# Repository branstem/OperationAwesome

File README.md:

OperationAwesome
================

ECE411 Project

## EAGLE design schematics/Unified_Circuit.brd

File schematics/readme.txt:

This folder was made for circuits.

All unique symbols not shipped with eaglecad should be added to symbols.lbr. 

This library file should also be added to eagles library path to load and 
edit the file.

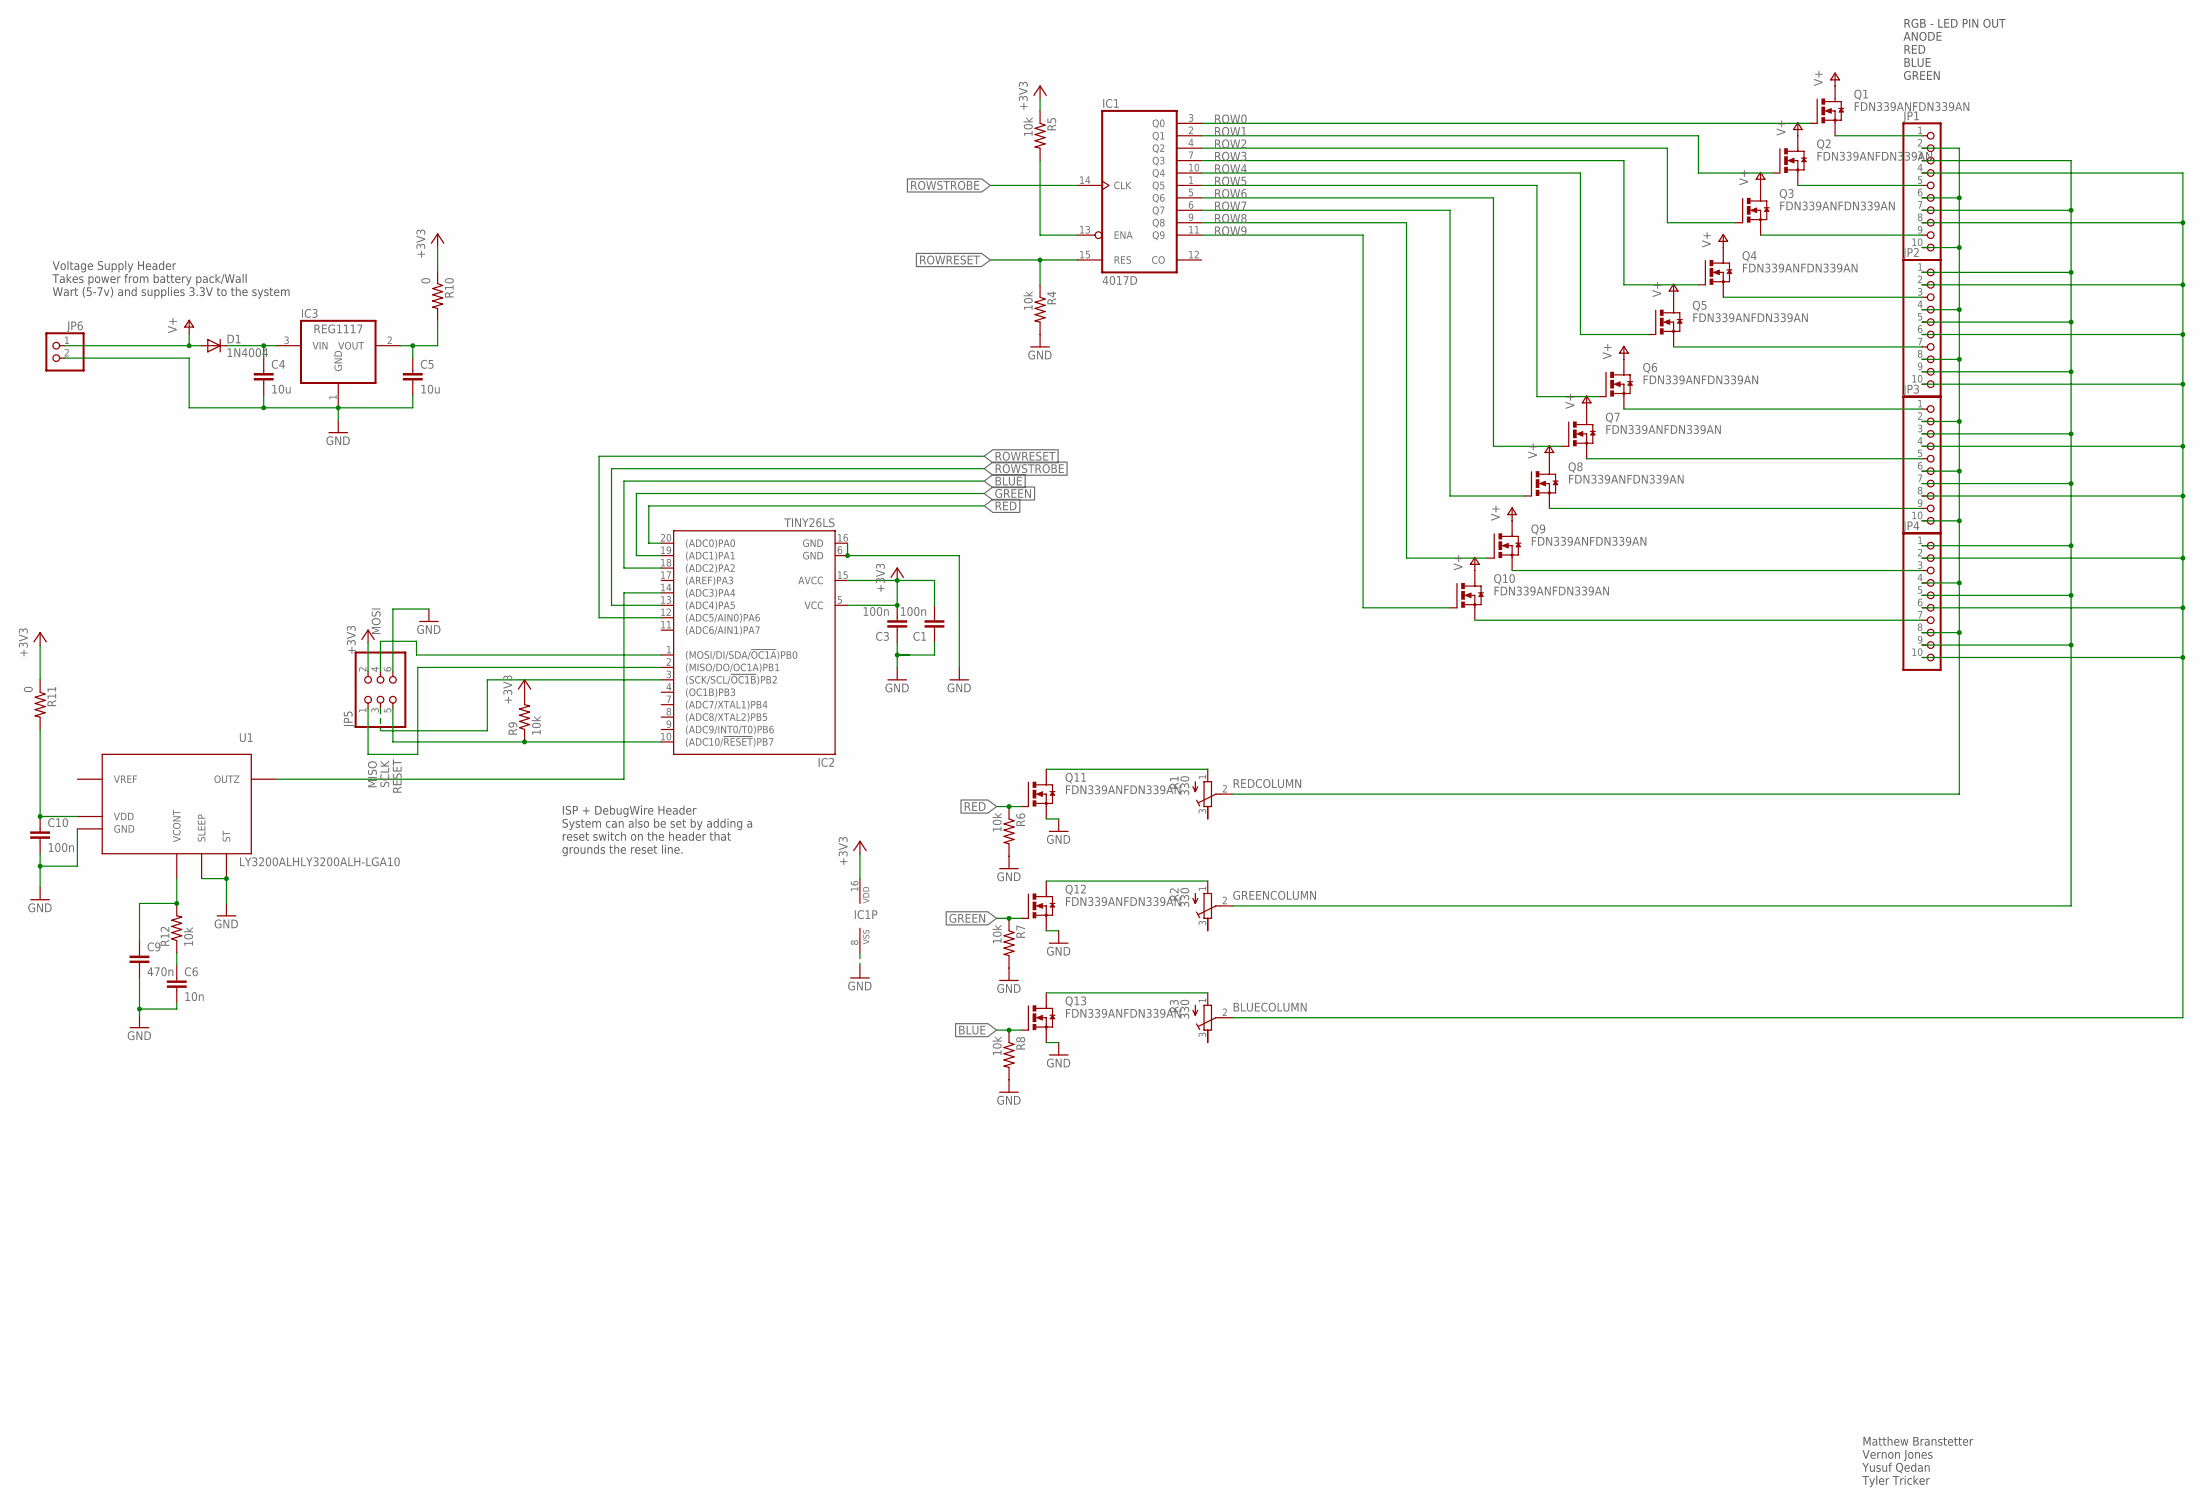
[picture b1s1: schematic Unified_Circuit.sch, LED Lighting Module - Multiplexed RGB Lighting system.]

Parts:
C1, C3, C10: 100n; C0805
C4, C5: 10u; C0805
C6: 10n; C0805
C9: 470n; C0805
D1: 1N4004; DO41-10
IC1: 4017D; SO16
IC2: TINY26LS; SO20L
IC3: REG1117; SOT223
JP1, JP2, JP3, JP4: PINHD-1X10/90; 1X10/90
JP5: PINHD-2X3; 2X03
JP6: PINHD-1X2; 1X02
Q1, Q2, Q3, Q4, Q5, Q6, Q7, Q8, Q9, Q10, Q11, Q12, Q13: FDN339ANFDN339AN; SSOT-3
R1, R2, R3: 330; RTRIM3224W
R4, R5, R6, R7, R8, R9, R12: 10k; R0805
R10, R11: 0; R0805
U1: LY3200ALHLY3200ALH-LGA10; LGA10

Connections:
+3V3: C1.2, C3.2, IC1.16 (VDD), IC2.5 (VCC), IC2.15 (AVCC), JP5.2, R5.1, R9.2, R10.1, R11.1
BLUE: IC2.18 ((ADC2)PA2), Q13.P$2 (G), R8.1
BLUECOLUMN: JP1.4, JP1.8, JP2.2, JP2.6, JP2.10, JP3.4, JP3.8, JP4.2, JP4.6, JP4.10, R3.2 (S)
GND: C1.1, C3.1, C4.2, C5.2, C6.2, C9.2, C10.2, IC1.8 (VSS), IC2.6 (GND), IC2.16 (GND), IC3.1 (GND), JP5.6, JP6.2, Q11.P$3 (S), Q12.P$3 (S), Q13.P$3 (S), R4.2, R6.2, R7.2, R8.2, U1.P$2 (ST), U1.P$4 (GND), U1.P$8 (SLEEP)
GREEN: IC2.19 ((ADC1)PA1), Q12.P$2 (G), R7.1
GREENCOLUMN: JP1.3, JP1.7, JP2.1, JP2.5, JP2.9, JP3.3, JP3.7, JP4.1, JP4.5, JP4.9, R2.2 (S)
MISO: IC2.2 ((MISO/DO/OC1A)PB1), JP5.1
MOSI: IC2.1 ((MOSI/DI/SDA/!OC1A!)PB0), JP5.4
unnamed: Q11.P$1 (D), R1.1 (A)
unnamed: Q12.P$1 (D), R2.1 (A)
unnamed: Q13.P$1 (D), R3.1 (A)
unnamed: C4.1, D1.C, IC3.3 (VIN)
unnamed: C5.1, IC3.2 (VOUT), R10.2
unnamed: IC2.14 ((ADC3)PA4), U1.P$6 (OUTZ)
unnamed: C6.1, R12.1
unnamed: JP2.3, Q4.P$3 (S)
unnamed: JP2.7, Q5.P$3 (S)
unnamed: JP1.1, Q1.P$3 (S)
unnamed: JP1.5, Q2.P$3 (S)
unnamed: JP1.9, Q3.P$3 (S)
unnamed: JP3.1, Q6.P$3 (S)
unnamed: JP3.5, Q7.P$3 (S)
unnamed: JP3.9, Q8.P$3 (S)
unnamed: JP4.3, Q9.P$3 (S)
unnamed: JP4.7, Q10.P$3 (S)
unnamed: C9.1, R12.2, U1.P$3 (VCONT)
unnamed: C10.1, R11.2, U1.P$1 (VDD), U1.P$9 (VDD)
PA1: IC1.13 (ENA), R5.2
RED: IC2.20 ((ADC0)PA0), Q11.P$2 (G), R6.1
REDCOLUMN: JP1.2, JP1.6, JP1.10, JP2.4, JP2.8, JP3.2, JP3.6, JP3.10, JP4.4, JP4.8, R1.2 (S)
RESET: IC2.10 ((ADC10/!RESET!)PB7), JP5.5, R9.1
ROW0: IC1.3 (Q0), Q1.P$2 (G)
ROW1: IC1.2 (Q1), Q2.P$2 (G)
ROW2: IC1.4 (Q2), Q3.P$2 (G)
ROW3: IC1.7 (Q3), Q4.P$2 (G)
ROW4: IC1.10 (Q4), Q5.P$2 (G)
ROW5: IC1.1 (Q5), Q6.P$2 (G)
ROW6: IC1.5 (Q6), Q7.P$2 (G)
ROW7: IC1.6 (Q7), Q8.P$2 (G)
ROW8: IC1.9 (Q8), Q9.P$2 (G)
ROW9: IC1.11 (Q9), Q10.P$2 (G)
ROWRESET: IC1.15 (RES), IC2.12 ((ADC5/AIN0)PA6), R4.1
ROWSTROBE: IC1.14 (CLK), IC2.13 ((ADC4)PA5)
SCLK: IC2.3 ((SCK/SCL/!OC1B!)PB2), JP5.3
V+: D1.A, JP6.1, Q1.P$1 (D), Q2.P$1 (D), Q3.P$1 (D), Q4.P$1 (D), Q5.P$1 (D), Q6.P$1 (D), Q7.P$1 (D), Q8.P$1 (D), Q9.P$1 (D), Q10.P$1 (D)

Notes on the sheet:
RGB - LED PIN OUT ANODE RED BLUE GREEN
ISP + DebugWire Header System can also be set by adding a reset switch on the header that grounds the reset line.
Voltage Supply Header Takes power from battery pack/Wall Wart (5-7v) and supplies 3.3V to the system
Matthew Branstetter Vernon Jones Yusuf Qedan Tyler Tricker

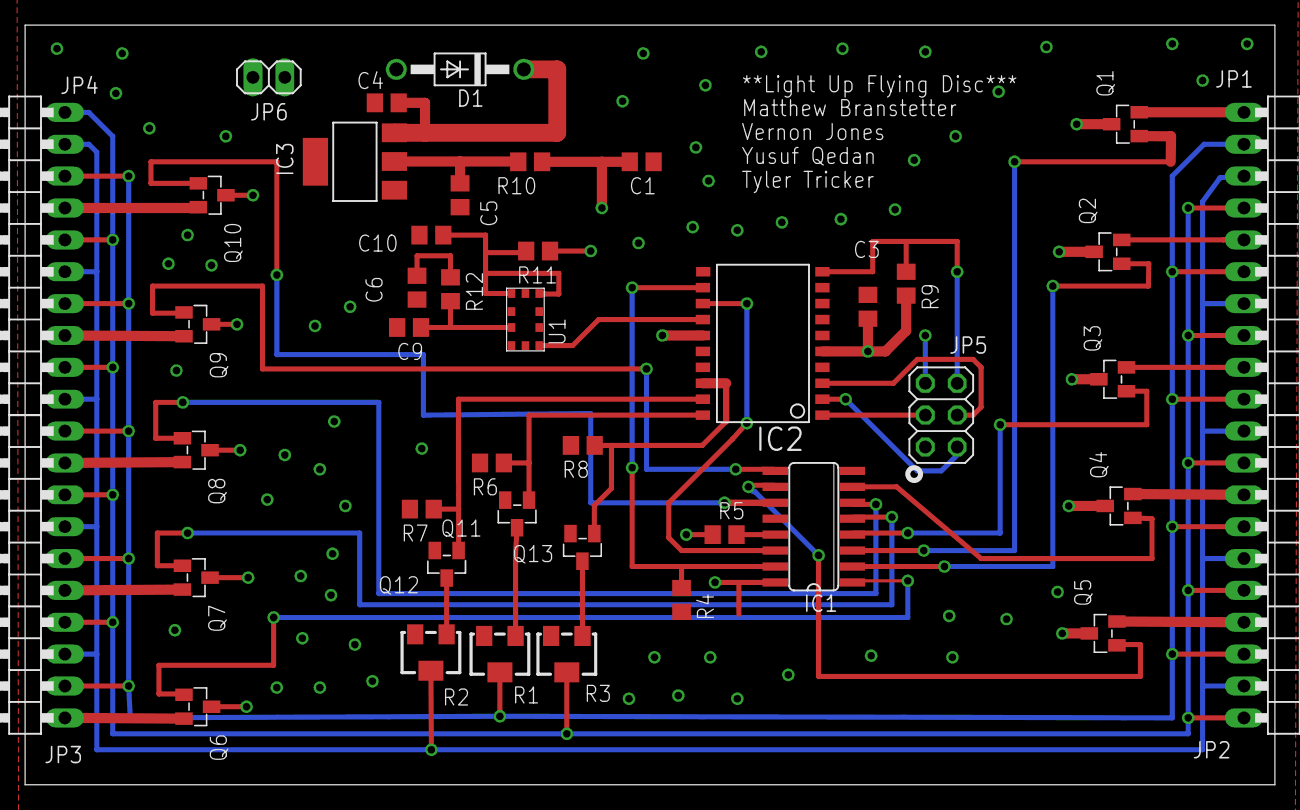
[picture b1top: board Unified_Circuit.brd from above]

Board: 2 copper layers, 99.6 x 60.6 mm, 43 parts (0 on the bottom side), 45 nets.

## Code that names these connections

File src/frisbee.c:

/*
 * frisbee.c
 *
 * Created: 10/12/2012 5:40:17 PM
 *  Author: Matthew, Vernon
 *
 * This program is free software; you can redistribute it and/or modify it
 * under the terms of the GNU Lesser General Public License as published by the
 * Free Software Foundation; either version 2.1 of the License, or (at your
 * option) any later version.
 *
 * This program is distributed in the hope that it will be useful, but
 * WITHOUT ANY WARRANTY; without even the implied warranty of
 * MERCHANTABILITY or FITNESS FOR A PARTICULAR PURPOSE.  See the GNU Lesser
 * General Public License for more details.
 *
 * You should have received a copy of the GNU Lesser General Public License along
 * with this program; if not, write to the Free Software Foundation, Inc.,
 * 51 Franklin Street, Fifth Floor, Boston, MA 02110-1301, USA.
 */


#include "frisbee.h"


void row_advance(void)
{
	// Advance to the next row
	setbit(PORTA, ROWSTROBE);
	_delay_us(10);
	//for (i=0; i<10; i++);
	clearbit(PORTA, ROWSTROBE);
}

void row_reset(void)
{
	// Reset to the first row
	setbit(PORTA, ROWRESET);
	//for (i=0; i<10; i++);
	_delay_us(10);
	clearbit(PORTA, ROWRESET);
}

void row_set_color (int red, int green, int blue)
{
	// Set the row color
	if (!PROTOTYPE)
	{
		red = !red;
		green = !green;
		blue = !blue;
	}
	if (red)
		clearbit(PORTA, LED_RED);
	else
		setbit(PORTA, LED_RED);

	// GREEN
	if (green)
		clearbit(PORTA, LED_GREEN);
	else
		setbit(PORTA, LED_GREEN);

	// BLUE
	if (blue)
		clearbit(PORTA, LED_BLUE);
	else
		setbit(PORTA, LED_BLUE);
	return;
}


void scheduler_run(struct sched_t sched[NUM_LEDS])
{
	int i;
	row_reset();
	for (i=0; i<NUM_LEDS; i++)
	{
		row_set_color(sched[i].red, sched[i].green, sched[i].blue);
		//row_set_color(1, 0, 0);
		_delay_us(200);
		//_delay_ms(1);
		//_delay_ms(1000);
		row_set_color(0, 0, 0);
		row_advance();
	}
	row_reset();
	
	return;
}

void scheduler_schedule_color(struct sched_t *sched, int red, int green, int blue)
{
	sched->red = red;
	sched->green = green;
	sched->blue = blue;
	
	return;
}

void scheduler_fill(struct sched_t sched[NUM_LEDS], int red, int green, int blue)
{
	int i;
	for (i=0; i<NUM_LEDS; i++)
		scheduler_schedule_color(&sched[i], red, green, blue);
		
	return;
}

void scheduler_rotate_left(struct sched_t sched[NUM_LEDS])
{
	int i, nexti;
	struct sched_t held_sched;
	scheduler_schedule_color(&held_sched, sched[NUM_LEDS-1].red, sched[NUM_LEDS-1].green, sched[NUM_LEDS-1].blue);
	for (i=NUM_LEDS-1; i>=0; i--)
	{
		nexti = (i-1) % NUM_LEDS;
		scheduler_schedule_color(&sched[i], sched[nexti].red, sched[nexti].green, sched[nexti].blue);
	}
	scheduler_schedule_color(&sched[0], held_sched.red, held_sched.green, held_sched.blue);
	return;
}

void scheduler_rotate_right(struct sched_t sched[NUM_LEDS])
{
	int i, nexti;
	struct sched_t held_sched;
	scheduler_schedule_color(&held_sched, sched[0].red, sched[0].green, sched[0].blue);
	for (i=0; i<NUM_LEDS; i++)
	{
		nexti = (i+1) % NUM_LEDS;
		scheduler_schedule_color(&sched[i], sched[nexti].red, sched[nexti].green, sched[nexti].blue);
	}
	scheduler_schedule_color(&sched[NUM_LEDS-1], held_sched.red, held_sched.green, held_sched.blue);
	return;
}

void scheduler_do_startup(struct sched_t sched[NUM_LEDS])
{
	int i, j;
	scheduler_fill(sched, 0, 0, 0);
	scheduler_schedule_color(&sched[0], 0, 1, 0);
	for (i=0; i<NUM_LEDS-1; i++)
	{
		for (j=0; j<60; j++)
			scheduler_run(sched);
		scheduler_rotate_left(sched);
	}
	for (i=0; i<NUM_LEDS; i++)
	{
		for (j=0; j<60; j++)
			scheduler_run(sched);
			
		scheduler_rotate_right(sched);
	}
	return;
}


void schedule_party_mode(struct sched_t sched[NUM_LEDS])
{
	int color = 0;
	int i;
	for (i=0; i<NUM_LEDS; i++)
	{
		switch (color)
		{
			case 0:
				scheduler_schedule_color(&sched[i], 1, 0, 0);
				break;
			case 1:
				scheduler_schedule_color(&sched[i], 0, 1, 0);
				break;
			case 2:
				scheduler_schedule_color(&sched[i], 0, 0, 1);
				break;
			default:
				scheduler_schedule_color(&sched[i], 1, 1, 1);
		}
		color = (color + 1) % 3;
	}
	return;
}
int init_microcontroller(void)
{
	init_ports();				// setup the ports
	init_ADC();					// setup the Analog Converter
	
	return 0;
}

void init_ports(void)
{
   setbit(DDRA, PA0);	// Set as output (LED_RED)
   setbit(DDRA, PA1);	// Set as output (LED_GREEN)
   setbit(DDRA, PA2);	// Set as output (LED_BLUE)
   clearbit(DDRA, PA3);	// Set as input AREF
   clearbit(DDRA, PA4);	// Set as input (ADC3)
   setbit(DDRA, PA5);	// Set as output (ROWSTROBE)
   setbit(DDRA, PA6);	// Set as output (ROWRESET)
   setbit(DDRA, PA7);	// Set as output 
   setbit(PORTA, PA7);
}

void init_ADC(void)
{
   setbit(ADCSRB, REFS2);	// Set voltage reference to internal 2.56V
   setbit(ADMUX, REFS1);	// Set voltage reference to internal 2.56V
   //clearbit(ADMUX, REFS1);	// Set voltage reference to internal 3.3V
   clearbit(ADMUX, REFS0);	// Set voltage reference to internal 2.56V 
   
   setbit(ADMUX, ADLAR);	// Left adjust ADC result to allow easy 8 bit reading
   
   //Using Single Conversion this code not needed
   //setbit(ADCSRA, ADATE);	// Set ADD to Auto Trigger enabled for free running
   
   setbit(ADCSRA, ADPS2);	// Set ADC pre-scalar to 64 (8 MHZ / 64 = 125 KHZ)
   setbit(ADCSRA, ADPS1);	// Set ADC pre-scalar to 64 (8 MHZ / 64 = 125 KHZ)
   clearbit(ADCSRA, ADPS0);	// Set ADC pre-scalar to 64 (8 MHZ / 64 = 125 KHZ)
   
   // clear junk out (do an initial read off ADC)
   clearbit(ADMUX, MUX4);	// Select channel ADC3
   clearbit(ADMUX, MUX3);	// Select channel ADC3
   clearbit(ADMUX, MUX2);	// Select channel ADC3
   setbit(ADMUX, MUX1);		// Select channel ADC3
   setbit(ADMUX, MUX0);		// Select channel ADC3
   
   setbit(ADCSRA, ADEN);	// Enable ADC
   setbit(ADCSRA, ADSC);	// Start AD Conversions
}


uint8_t read_ADC(void)
{
	clearbit(ADMUX, MUX4);			// Select channel ADC3
	clearbit(ADMUX, MUX3);			// Select channel ADC3
	clearbit(ADMUX, MUX2);			// Select channel ADC3
	setbit(ADMUX, MUX1);			// Select channel ADC3
	setbit(ADMUX, MUX0);			// Select channel ADC3
	
	setbit(ADCSRA, ADSC);			// Start AD Conversions
	while(!(ADCSRA & (1<<ADIF)));	// Wait for conversion to complete
	setbit(ADCSRA, ADIF);			// Set flag AD conversion complete
	return ADCH;					// Return the 8 bit value
}

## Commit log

2013-12-03 Cloned Repository from cloud.
